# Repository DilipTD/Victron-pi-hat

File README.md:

# Victron Raspberry Pi HAT (v45.3)

A 4-layer, 85 x 56 mm Raspberry Pi 5 HAT for Victron Venus OS. It adds three VE.Direct ports, VE.Can, RS485, four low-side relay outputs, four opto-isolated inputs, a fan output, a buzzer and a plug-on 5 V / 5 A supply for the Pi, all fed from a 7-40 V battery input. Fabrication: JLCPCB. Designer: Dilip Kumar TD.

## 1. Key specification

| Item | Value |
|---|---|
| Board | 85 x 56 mm, 4 layers, 1.6 mm, KiCad 7 |
| Input | 7-40 V DC at J101, 7 A fuse F101 |
| 5 V supply | 7Semi AP64500 plug-on module U201, fixed 5.0 V, 5 A, on 5 mm pins |
| Pi | Raspberry Pi 5 (Venus OS v3.70+, raspberrypi5 image), powered only through the HAT |
| Ports | VE.Direct x3 (J301, J302, J401), RS485 (J402), VE.Can (J501), 4 relay outputs (J601), 4 opto inputs 5-30 V (J701), fan (J602) |
| Chips | 2x SC16IS752 (UARTs), MCP2515 + SN65HVD230 (CAN), SP3485 (RS485), ULN2003A (relay drivers), TLP290-4 (opto inputs), 24LC32A (HAT ID EEPROM) |
| Protection | 7 A fuse F101, 5 V TVS D201 (P6SMB6.8CA). No reverse-polarity protection and no input TVS: check polarity before connecting |

## 2. PCB design

**Stack-up (JLCPCB 4-layer, 1.6 mm):** F.Cu signals and parts, In1.Cu solid GND plane, In2.Cu +5V plane, B.Cu signals, parts and power pours. Copper: 1 oz outer, 0.5 oz inner (JLCPCB default stack-up).

**Power paths:**
- Input VIN_RAW / VIN_F / VIN_P: 1.6 mm tracks plus B.Cu pours in parallel, joined by 0.8 / 0.4 mm via arrays, sized for 4.2 A (7 V in, 5 A out).
- +5V: pours at the module output pins, then the In2.Cu +5V plane. In v45.3 the +5V also continues on F.Cu and In1.Cu at the Pi supply corner, with a copper bridge (26.5-34.5 x 58-68.5 mm) and an In1.Cu +5V pour at the U201 output (wider copper where the supply narrows).
- GND: solid In1.Cu plane, F.Cu and B.Cu pours, stitching vias on a 3 mm grid.
- 5 V branches: Pi 2.5 A, display 3 A (PTC F102), relays and fan 2 A (PTC F601).

**Signals:**
- Net classes are stored in `victron-hat.kicad_pro` (see `01-PCB-v45.0/NETCLASSES.md`): signals 0.20 mm track, 0.15 mm clearance; fieldbus pairs (CAN, RS485) 0.4 mm with 0.30 mm clearance; VE.Direct pairs 0.25 mm; pour-free corridors beside the pairs.
- Vias: 0.6 / 0.3 mm for signals, 0.8 / 0.4 mm for power, 1.0 / 0.5 mm groups for high current.
- U201 is a THT module on 5 mm pins: pins 1-3 VIN, 4-9 GND, 10-12 +5V, with 1.8 mm pads.

**Manufacturing:** JLCPCB Gerber zip, BOM and CPL are in `01-PCB-v45.0/JLCPCB/` (bottom-side economic assembly). Hand-soldered parts are listed in `HAND-SOLDER-parts.csv` (terminals, JST connectors, Pi socket, buzzer, U201 pins). Silkscreen is clipped from pads, pin-1 marks are chamfered pads, and diode cathodes are marked by a bar.

**Checks:** KiCad DRC 0 errors / 0 unconnected / 0 footprint errors on v45.3. JLCPCB's own JLCDFM and 3D assembly preview have not been run: upload the Gerber zip there before paying. Known JLCDFM items: mask-opening and "( )" warnings, and a 2.40 mm THT-to-SMD gap between U201 pin 1 and IC701 pin 9 (warning).

## 3. Voltage drop (DC copper solve, full 5 A load, v45.3)

| Net | Result |
|---|---|
| +5V output, 5.0 A total | max drop 12.6 mV at the Pi header (J201), 5.7 mV display, 5.2 mV relay; copper loss 0.047 W |
| GND return | max drop 5.1 mV; copper loss 0.022 W |
| VIN_RAW / VIN_P | a few mV (see `01-PCB-v45.0/SIMULATION`) |

Current density peaks: +5V In2 1.02 A/mm, GND In1 1.93 A/mm (above the 1.25 A/mm inner-layer guide, in a few small spots between the Pi header GND pins), GND F.Cu 2.45 A/mm (limit 2.5). The Pi header gets about 4.98 V at 5 A with U201 at 5.00 V.

## 4. Thermal

Method: 2-D thermal sheet model of the board (0.25 mm grid), component losses plus copper I2R plus the U201 module loss, with still air or a 30 mm fan. Modelled; not measured on hardware.

| Case | Result |
|---|---|
| Copper I2R only, 5 A | temperature rise at most about 1 C |
| HAT with all ICs, U201 module excluded, 40 V in, 60 C ambient | stays below 70 C |
| U201 module itself at 5 A | loses 2.4-4.7 W; about 71-111 C with fan at 25 C ambient, up to about 131-187 C in still air at 60 C ambient |

**The 5 V module is the hot spot, not the board copper.** For a continuous 5 A load, fit a heatsink on U201, add copper under it, keep the fan fitted (30 mm fan over the 28 mm cutout), or limit the continuous load to about 3 A. Reports and heat maps: `01-PCB-v45.0/SIMULATION/` (THERMAL-*.md and thermal-*.png).

## 5. Port simulation

Calculated from the routed v45.3 board: series resistors, edge times, fault currents and routed lengths for every port.

- VE.Direct (3.3 V logic, 470 R series): TX high 3.25 V; a shorted TX pin draws about 7 mA, within the SC16IS752 limit; 5 V Victron TX is accepted (5 V-tolerant input).
- RS485 (SP3485) and CAN (SN65HVD230 + MCP2515): equal-length pairs, 120 R termination by jumper (JP401 / JP501, bus end only).
- Track-length skew between signals is at most about 0.1 ns, negligible against the slowest bit time (2 us for CAN at 500 kbit/s).
- Opto inputs: apply 5-30 V DC between INx and IN COM.

## 6. Venus OS GUI

The screenshots are layout renderings with example values, not captures from real hardware. Classic GUI pages: [ALL-GUI-v1-classic-pages.png](03-GUI-screenshots/ALL-GUI-v1-classic-pages.png)

## 7. 4-relay extension board

## 8. Install (Venus OS)

1. Write the HAT ID EEPROM once from Raspberry Pi OS (bridge JP801, run `eeprom/flash-eeprom.sh`).
2. On Venus OS install kwindrem SetupHelper, then:

```
scp -r 02-VenusOS-software-v4.2 root@venus.local:/data/VictronHat
ssh root@venus.local /data/VictronHat/setup
```

3. Choose Install, reboot, then Settings > Services > VE.Can port > "VE.Can & Lynx Ion BMS".
4. Relays and inputs need kwindrem RpiGpioSetup. Test on a spare SD card first.

Port wiring: J101 7-40 V (1 = -, 2 = +); J301/J302/J401 VE.Direct JST PH 4-pin; J402 RS485 A/B/GND; J501 CANH/CANL/GND; J601 OUT1-4 (0.5 A each, low-side), +5V, GND; J701 IN COM, IN1-IN4; J602 fan 5 V. Never plug USB-C into the Pi with the HAT fitted.

## 9. Contents

| Path | Content |
|---|---|
| 01-PCB-v45.0/ | Gerbers, BOM, CPL, Schematic, checks |
| 01-PCB-v45.0/JLCPCB/ | Gerber zip to upload to JLCPCB |
| 02-VenusOS-software-v4.2/ | Venus OS package (SetupHelper) and HAT EEPROM |
| 03-GUI-screenshots/, 04-3D-preview/ | GUI renderings, 3D preview |
| 05-relay-extension-v1.2/ | relay extension board |
| 07-tool-pcb-autorouter/ | Python autorouter |

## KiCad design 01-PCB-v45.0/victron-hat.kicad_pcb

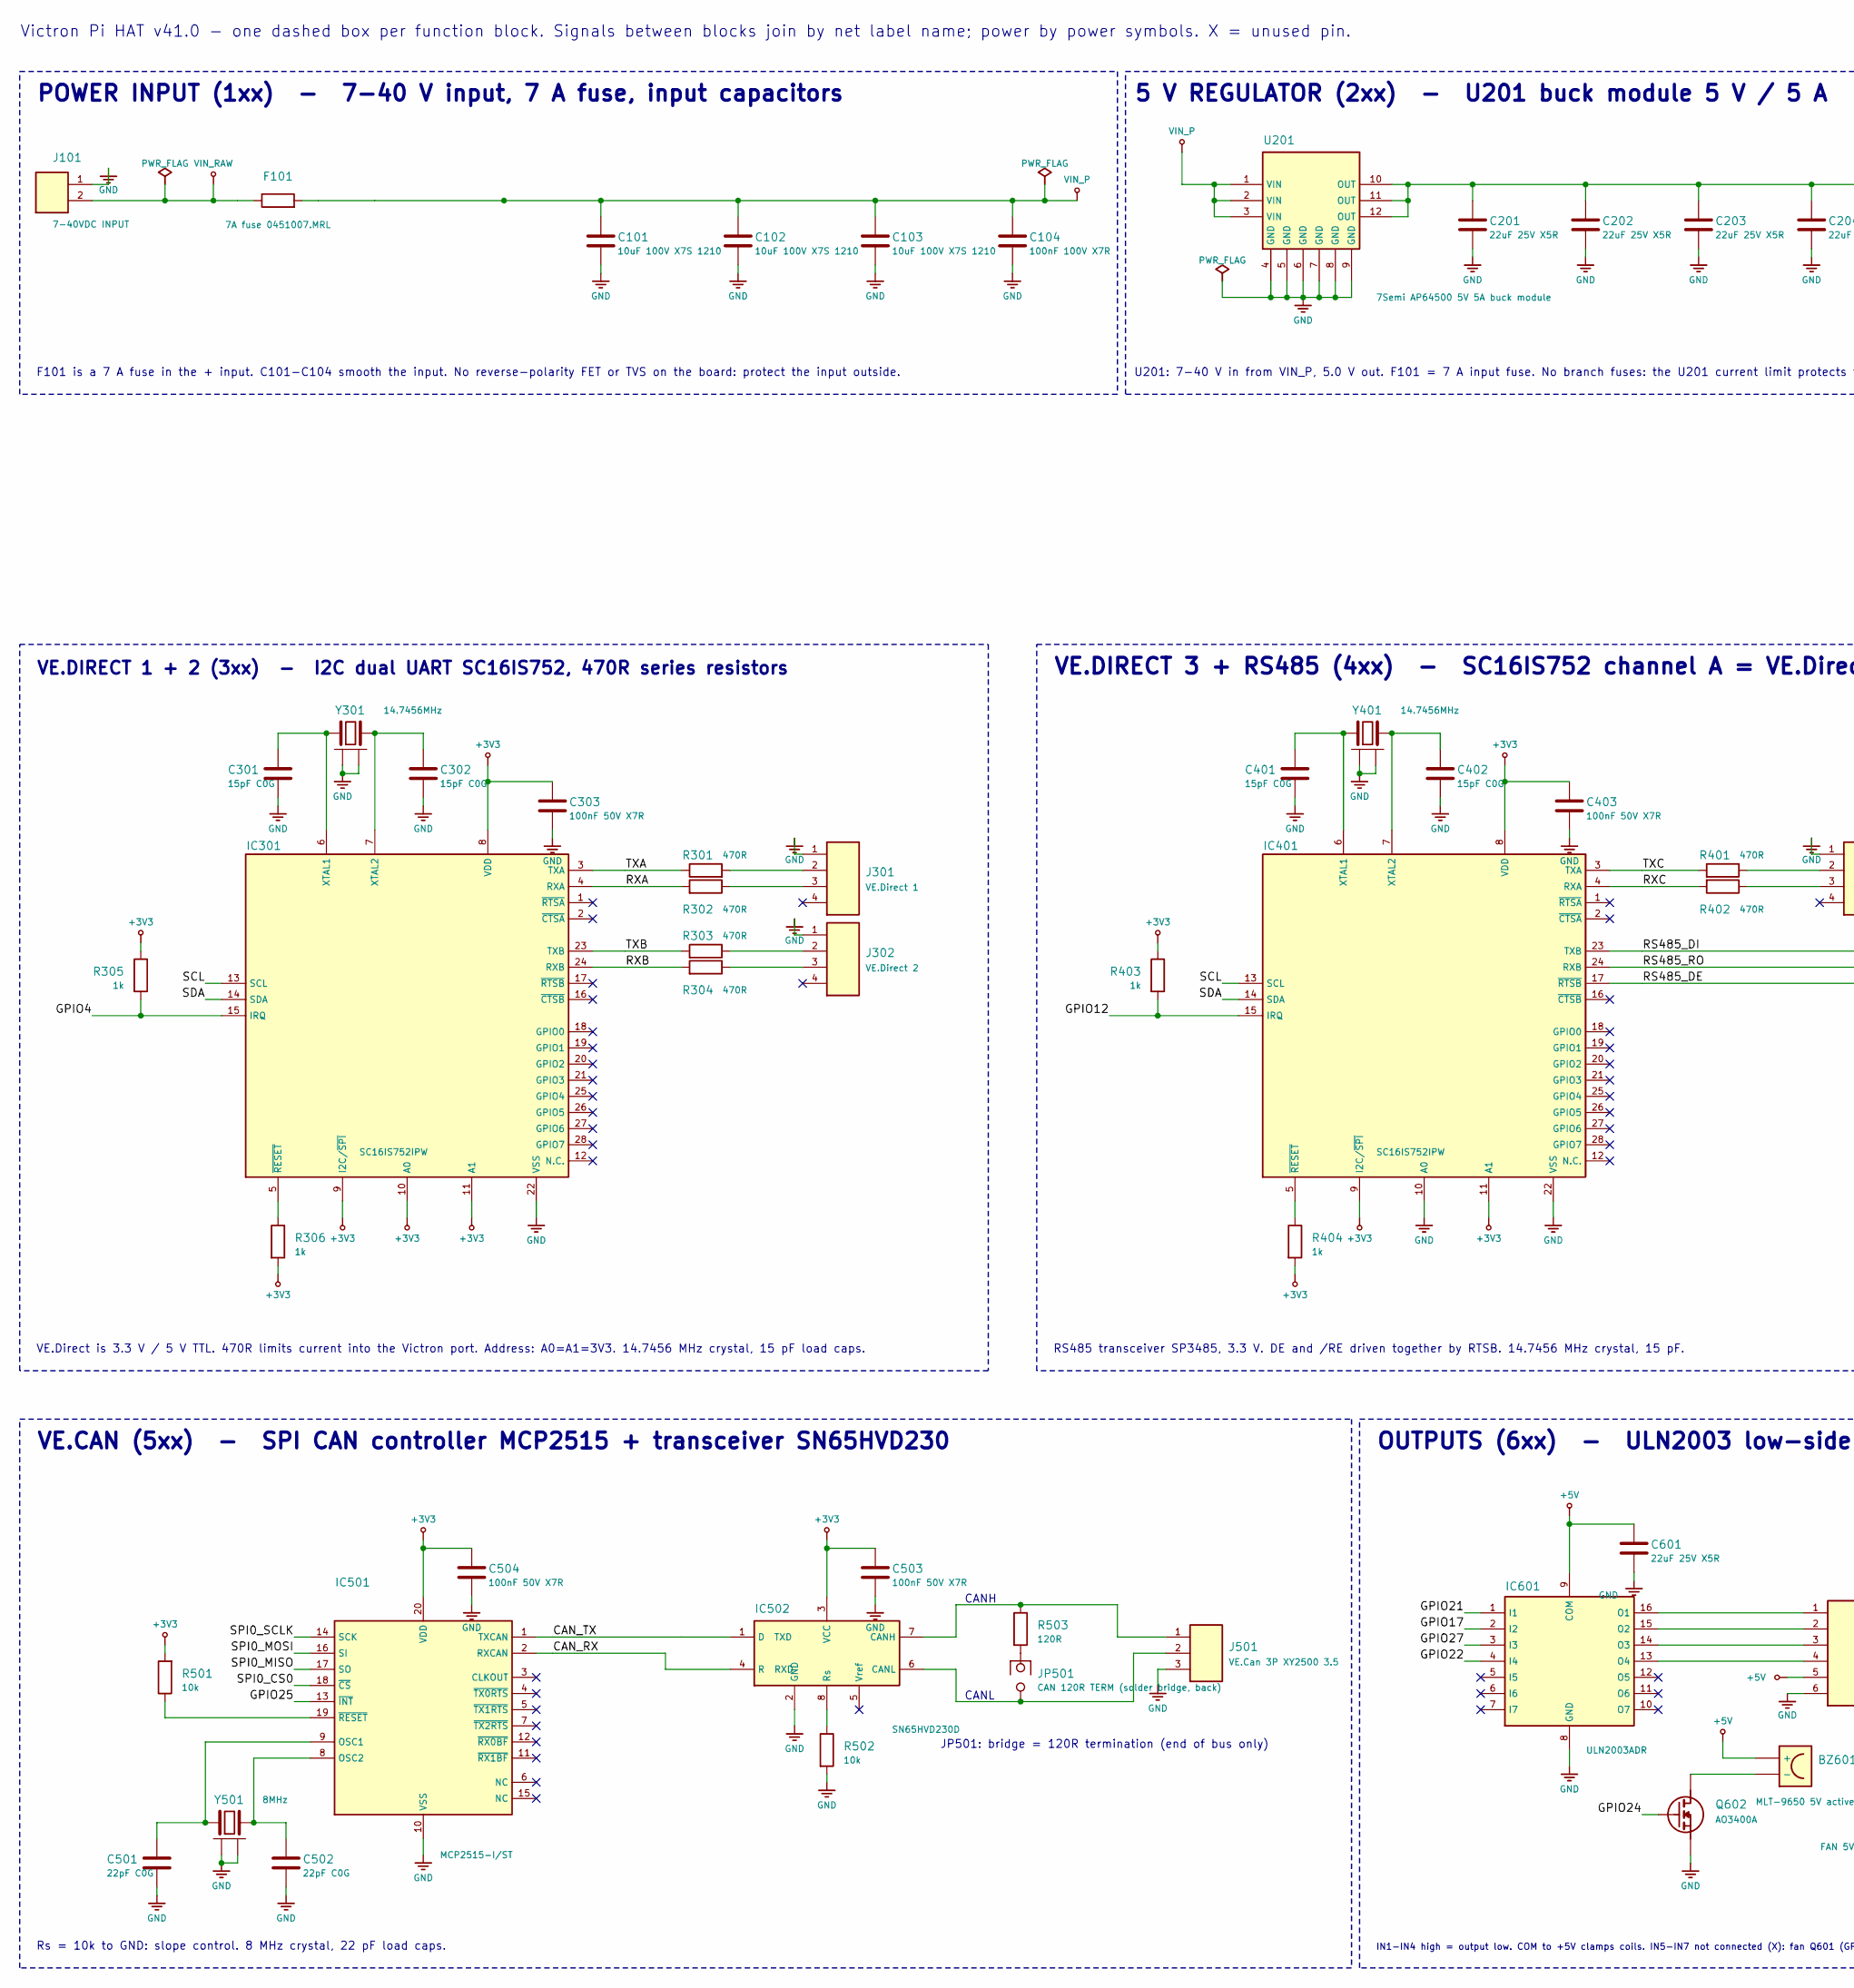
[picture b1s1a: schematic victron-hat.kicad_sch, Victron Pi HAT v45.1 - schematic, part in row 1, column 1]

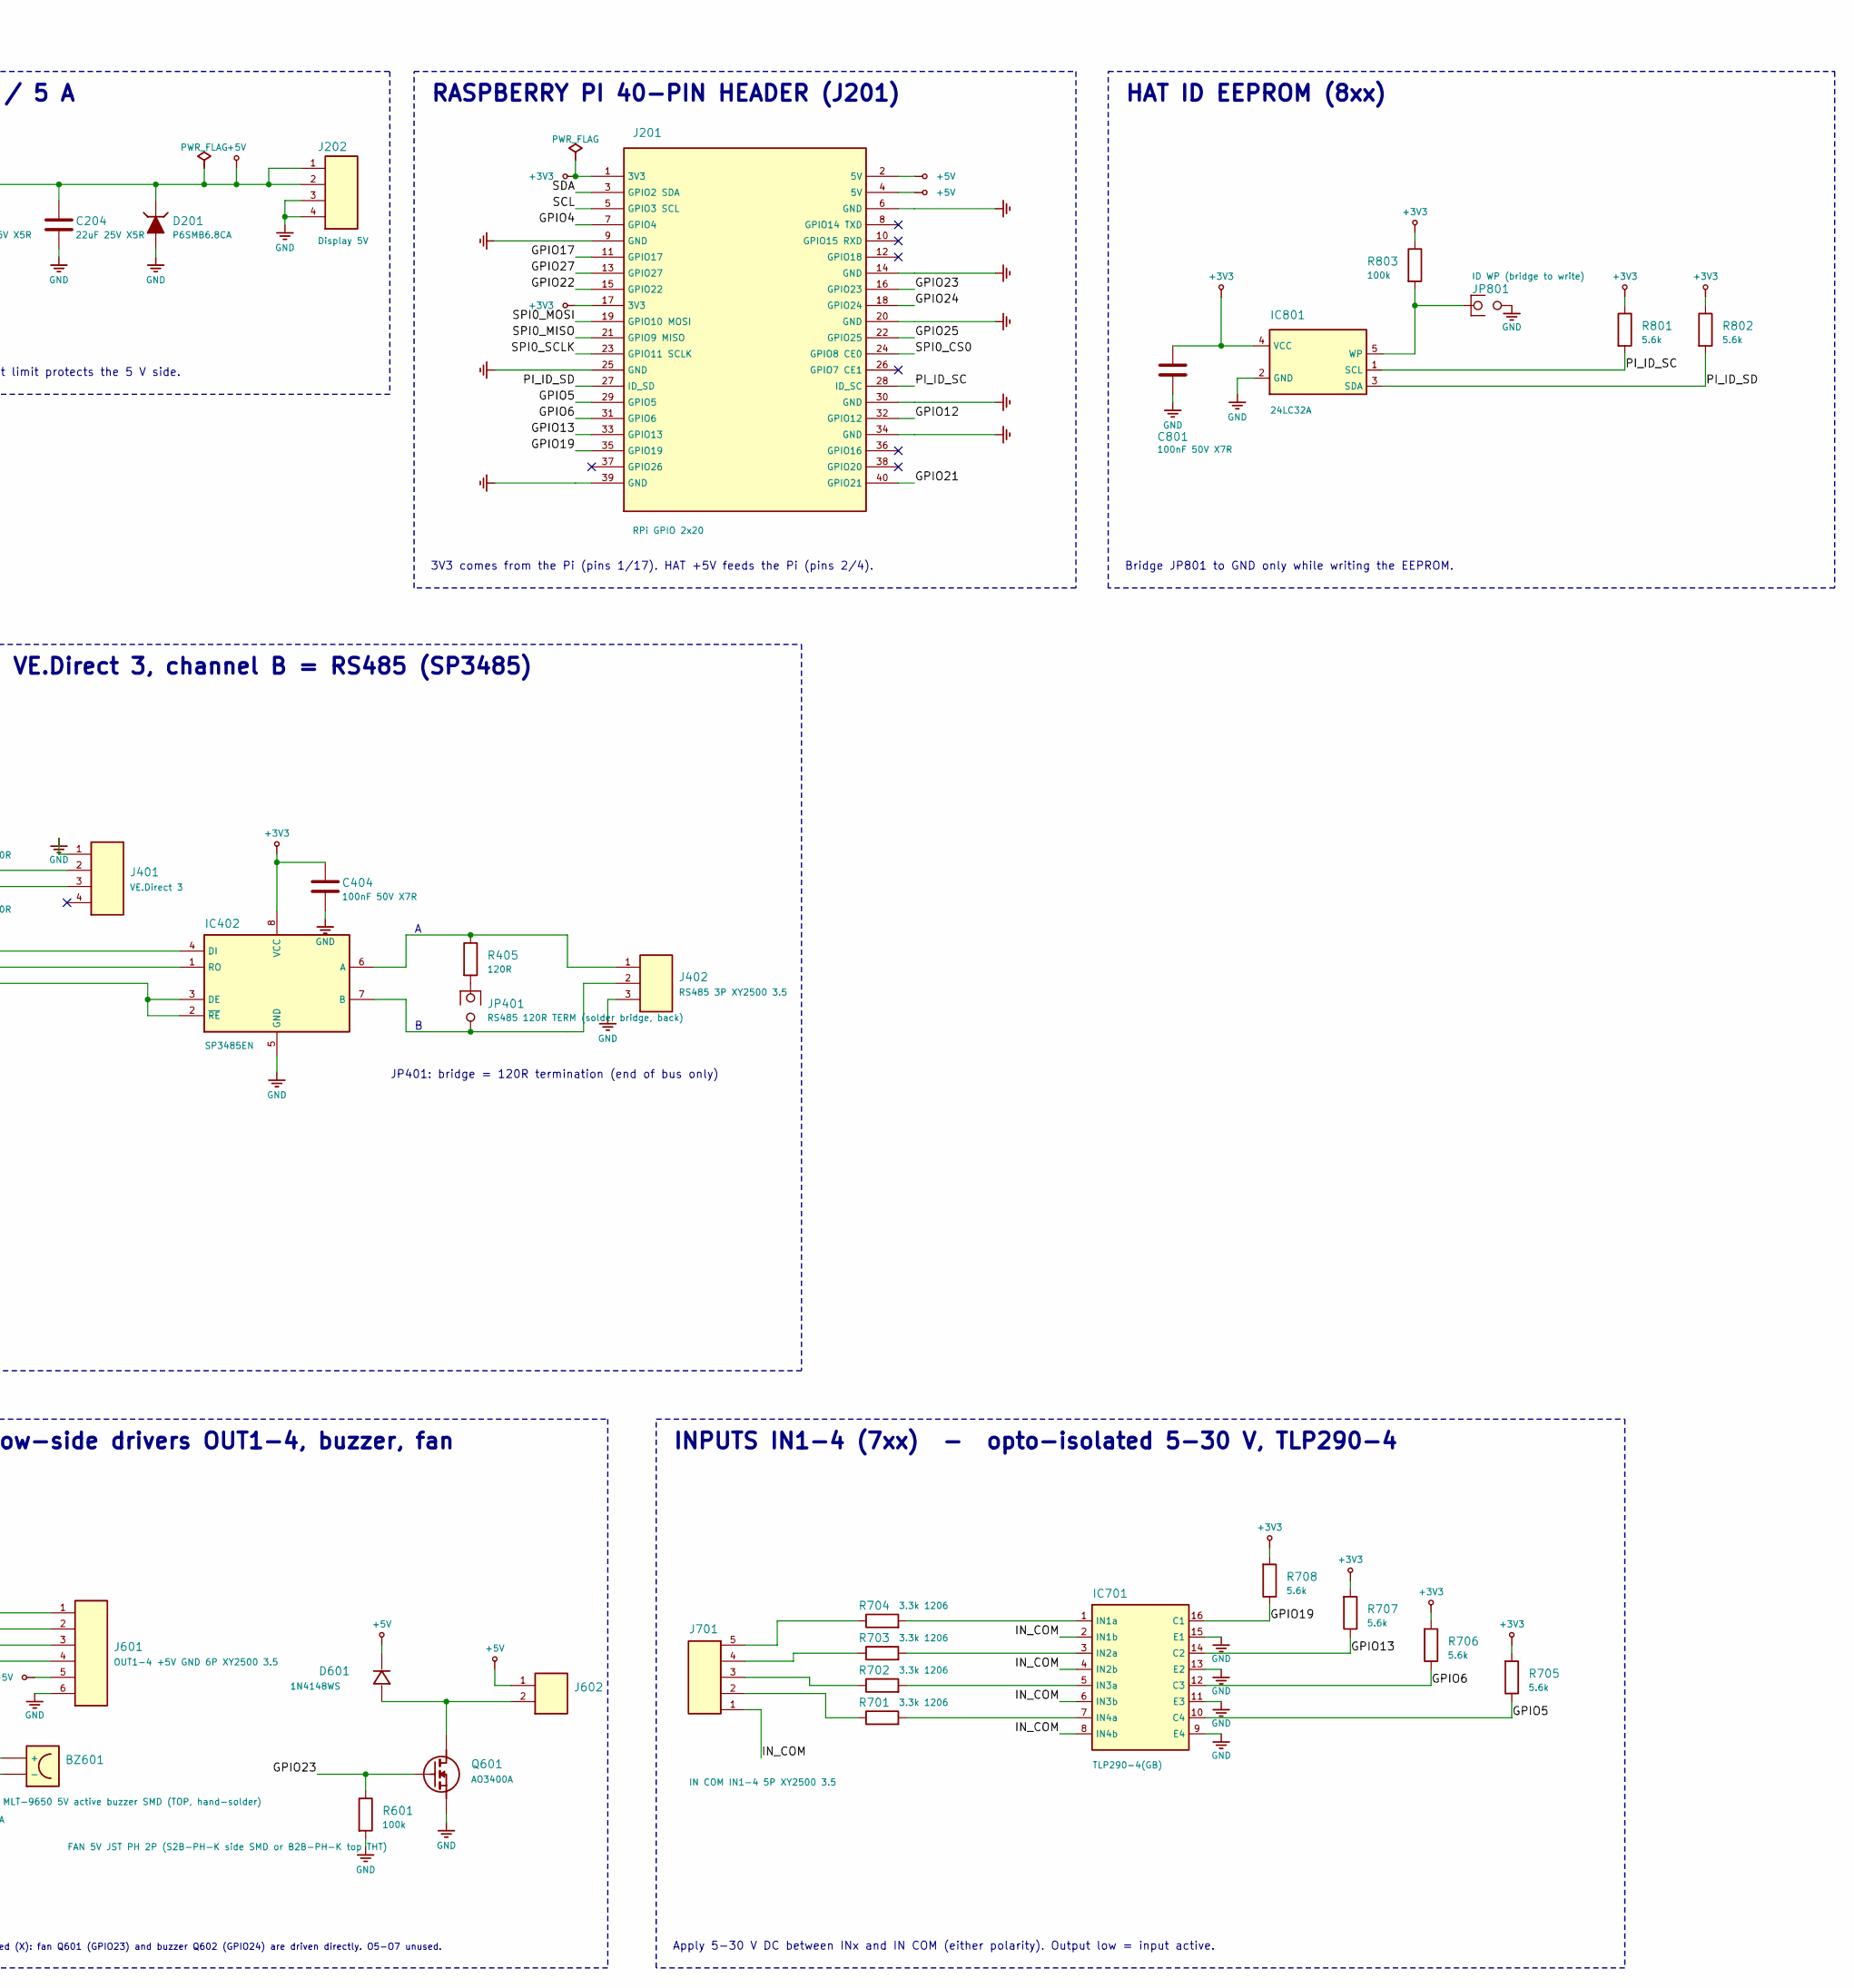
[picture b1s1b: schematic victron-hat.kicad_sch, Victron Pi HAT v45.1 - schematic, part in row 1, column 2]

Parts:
BZ601: MLT-9650 5V active buzzer SMD (TOP, hand-solder); Buzzer_SMD_9.6x9.6mm_MLT-9650; LCSC C96127
C101, C102, C103: 10uF 100V X7S 1210; C_1210_3225Metric; LCSC C576517
C104: 100nF 100V X7R; C_0805_2012Metric; LCSC C28233
C201, C202, C203, C204, C601: 22uF 25V X5R; C_0805_2012Metric; LCSC C45783
C301, C302, C401, C402: 15pF C0G; C_0805_2012Metric; LCSC C63339
C303, C403, C404, C503, C504, C801: 100nF 50V X7R; C_0805_2012Metric; LCSC C49678
C501, C502: 22pF C0G; C_0805_2012Metric; LCSC C1804
D201: P6SMB6.8CA; D_SMB; LCSC C78395
D601: 1N4148WS; D_SOD-323; LCSC C2128
F101: 7A fuse 0451007.MRL; Fuse_Littelfuse-NANO2-451_453; LCSC hand-solder
IC301, IC401: SC16IS752IPW; TSSOP-28_4.4x9.7mm_P0.65mm; LCSC C57156
IC402: SP3485EN; SOIC-8_3.9x4.9mm_P1.27mm; LCSC C8963
IC501: MCP2515-I/ST; TSSOP-20_4.4x6.5mm_P0.65mm; LCSC C185941
IC502: SN65HVD230D; SOIC-8_3.9x4.9mm_P1.27mm; LCSC C12084
IC601: ULN2003ADR; SOIC-16_3.9x9.9mm_P1.27mm; LCSC C7512
IC701: TLP290-4(GB); SOP-16_4.4x10.3mm_P1.27mm; LCSC C39031
IC801: 24LC32A; SOT-23-5; LCSC C616245
J101: 7-40VDC INPUT; PhoenixContact_MC_1,5_2-G-3.5_1x02_P3.50mm_Horizontal; LCSC C880572
J201: RPi GPIO 2x20; PinSocket_2x20_P2.54mm_Vertical
J202: Display 5V; PinHeader_1x04_P2.54mm_Vertical; LCSC C124378
J301: VE.Direct 1; JST_PH_S4B-PH-K_1x04_P2.00mm_Horizontal; LCSC C157926
J302: VE.Direct 2; JST_PH_S4B-PH-K_1x04_P2.00mm_Horizontal; LCSC C157926
J401: VE.Direct 3; JST_PH_S4B-PH-K_1x04_P2.00mm_Horizontal; LCSC C157926
J402: RS485 3P XY2500 3.5; PhoenixContact_MC_1,5_3-G-3.5_1x03_P3.50mm_Horizontal; LCSC C880573
J501: VE.Can 3P XY2500 3.5; PhoenixContact_MC_1,5_3-G-3.5_1x03_P3.50mm_Horizontal; LCSC C880573
J601: OUT1-4 +5V GND 6P XY2500 3.5; PhoenixContact_MC_1,5_6-G-3.5_1x06_P3.50mm_Horizontal
J602: FAN 5V JST PH 2P (S2B-PH-K side SMD or B2B-PH-K t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; JST_PH_S2B-PH-K_1x02_P2.00mm_Horizontal; LCSC C173752
J701: IN COM IN1-4 5P XY2500 3.5; PhoenixContact_MC_1,5_5-G-3.5_1x05_P3.50mm_Horizontal; LCSC C880575
JP401: RS485 120R TERM (solder bridge, back); SolderJumper-2_P1.3mm_Open_RoundedPad1.0x1.5mm
JP501: CAN 120R TERM (solder bridge, back); SolderJumper-2_P1.3mm_Open_RoundedPad1.0x1.5mm
JP801: ID WP (bridge to write); SolderJumper-2_P1.3mm_Open_RoundedPad1.0x1.5mm
Q601, Q602: AO3400A; SOT-23; LCSC C20917
R301, R302, R303, R304, R401, R402: 470R; R_0805_2012Metric; LCSC C17710
R305, R306, R403: 1k; R_0805_2012Metric; LCSC C17513
R404: 1k; R_0603_1608Metric; LCSC C21190
R405, R503: 120R; R_0805_2012Metric; LCSC C17437
R501, R502: 10k; R_0805_2012Metric; LCSC C17414
R601, R803: 100k; R_0603_1608Metric; LCSC C25803
R701, R702, R703, R704: 3.3k 1206; R_1206_3216Metric; LCSC C26032
R705, R706, R707, R708, R801, R802: 5.6k; R_0603_1608Metric; LCSC C23189
U201: 7Semi AP64500 5V 5A buck module; 7Semi_AP64500_Module_21x18mm
Y301, Y401: 14.7456MHz; Crystal_SMD_3225-4Pin_3.2x2.5mm; LCSC C2885591
Y501: 8MHz; Crystal_SMD_3225-4Pin_3.2x2.5mm; LCSC C2682775

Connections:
+3V3: C303.1, C403.1, C404.1, C503.1, C504.1, C801.1, IC301.8 (VDD), IC301.9 (I2C/~SPI), IC301.10 (A0), IC301.11 (A1), IC401.8 (VDD), IC401.9 (I2C/~SPI), IC401.11 (A1), IC402.8 (VCC), IC501.20 (VDD), IC502.3 (VCC), IC801.4 (VCC), J201.1 (3V3), J201.17 (3V3), R305.1, R306.2, R403.1, R404.2, R501.2, R705.1, R706.1, R707.1, R708.1, R801.1, R802.1, R803.1
+5V: BZ601.1 (+), C201.1, C202.1, C203.1, C204.1, C601.1, D201.1 (K), D601.1 (K), IC601.9 (COM), J201.2 (5V), J201.4 (5V), J202.1, J202.2, J601.5, J602.1, U201.10 (OUT), U201.11 (OUT), U201.12 (OUT)
/CAN_RX: IC501.2 (RXCAN), IC502.4 (R RXD)
/CAN_TX: IC501.1 (TXCAN), IC502.1 (D TXD)
/GPIO4: IC301.15 (IRQ), J201.7 (GPIO4), R305.2
/GPIO5: IC701.10 (C4), J201.29 (GPIO5), R705.2
/GPIO6: IC701.12 (C3), J201.31 (GPIO6), R706.2
/GPIO12: IC401.15 (IRQ), J201.32 (GPIO12), R403.2
/GPIO13: IC701.14 (C2), J201.33 (GPIO13), R707.2
/GPIO17: IC601.2 (I2), J201.11 (GPIO17)
/GPIO19: IC701.16 (C1), J201.35 (GPIO19), R708.2
/GPIO21: IC601.1 (I1), J201.40 (GPIO21)
/GPIO22: IC601.4 (I4), J201.15 (GPIO22)
/GPIO23: J201.16 (GPIO23), Q601.1 (G), R601.1
/GPIO24: J201.18 (GPIO24), Q602.1 (G)
/GPIO25: IC501.13 (~INT), J201.22 (GPIO25)
/GPIO27: IC601.3 (I3), J201.13 (GPIO27)
/IN_COM: IC701.2 (IN1b), IC701.4 (IN2b), IC701.6 (IN3b), IC701.8 (IN4b), J701.1
/PI_ID_SC: IC801.1 (SCL), J201.28 (ID_SC), R801.2
/PI_ID_SD: IC801.3 (SDA), J201.27 (ID_SD), R802.2
/RS485_DE: IC401.17 (~RTSB), IC402.2 (~RE), IC402.3 (DE)
/RS485_DI: IC401.23 (TXB), IC402.4 (DI)
/RS485_RO: IC401.24 (RXB), IC402.1 (RO)
/RXA: IC301.4 (RXA), R302.2
/RXB: IC301.24 (RXB), R304.2
/RXC: IC401.4 (RXA), R402.2
/SCL: IC301.13 (SCL), IC401.13 (SCL), J201.5 (GPIO3 SCL)
/SDA: IC301.14 (SDA), IC401.14 (SDA), J201.3 (GPIO2 SDA)
/SPI0_CS0: IC501.18 (~CS), J201.24 (GPIO8 CE0)
/SPI0_MISO: IC501.17 (SO), J201.21 (GPIO9 MISO)
/SPI0_MOSI: IC501.16 (SI), J201.19 (GPIO10 MOSI)
/SPI0_SCLK: IC501.14 (SCK), J201.23 (GPIO11 SCLK)
/TXA: IC301.3 (TXA), R301.1
/TXB: IC301.23 (TXB), R303.1
/TXC: IC401.3 (TXA), R401.1
GND: C101.2, C102.2, C103.2, C104.2, C201.2, C202.2, C203.2, C204.2, C301.2, C302.2, C303.2, C401.2, C402.2, C403.2, C404.2, C501.2, C502.2, C503.2, C504.2, C601.2, C801.2, D201.2 (A), IC301.22 (VSS), IC401.10 (A0), IC401.22 (VSS), IC402.5 (GND), IC501.10 (VSS), IC502.2 (GND), IC601.8 (GND), IC701.9 (E4), IC701.11 (E3), IC701.13 (E2), IC701.15 (E1), IC801.2 (GND), J101.1, J201.6 (GND), J201.9 (GND), J201.14 (GND), J201.20 (GND), J201.25 (GND), J201.30 (GND), J201.34 (GND), J201.39 (GND), J202.3, J202.4, J301.1, J302.1, J401.1, J402.3, J501.3, J601.6, JP801.2, Q601.2 (S), Q602.2 (S), R502.2, R601.2, U201.4 (GND), U201.5 (GND), U201.6 (GND), U201.7 (GND), U201.8 (GND), U201.9 (GND), Y301.2 (GND), Y301.4 (GND), Y401.2 (GND), Y401.4 (GND), Y501.2 (GND), Y501.4 (GND)
unnamed: BZ601.2 (-), Q602.3 (D)
unnamed: D601.2 (A), J602.2, Q601.3 (D)
unnamed: C301.1, IC301.6 (XTAL1), Y301.3
unnamed: C302.1, IC301.7 (XTAL2), Y301.1
unnamed: IC301.5 (~RESET), R306.1
unnamed: C401.1, IC401.6 (XTAL1), Y401.3
unnamed: C402.1, IC401.7 (XTAL2), Y401.1
unnamed: IC401.5 (~RESET), R404.1
unnamed: IC402.6 (A), J402.1, R405.1
unnamed: IC402.7 (B), J402.2, JP401.2
unnamed: C501.1, IC501.9 (OSC1), Y501.3
unnamed: C502.1, IC501.8 (OSC2), Y501.1
unnamed: IC501.19 (~RESET), R501.1
unnamed: IC502.7 (CANH), J501.1, R503.1
unnamed: IC502.6 (CANL), J501.2, JP501.2
unnamed: IC502.8 (Rs), R502.1
unnamed: IC601.16 (O1), J601.1
unnamed: IC601.15 (O2), J601.2
unnamed: IC601.14 (O3), J601.3
unnamed: IC601.13 (O4), J601.4
unnamed: IC701.1 (IN1a), R704.2
unnamed: IC701.3 (IN2a), R703.2
unnamed: IC701.5 (IN3a), R702.2
unnamed: IC701.7 (IN4a), R701.2
unnamed: IC801.5 (WP), JP801.1, R803.2
unnamed: J301.2, R301.2
unnamed: J301.3, R302.1
unnamed: J302.2, R303.2
unnamed: J302.3, R304.1
unnamed: J401.2, R401.2
unnamed: J401.3, R402.1
unnamed: J701.2, R701.1
unnamed: J701.3, R702.1
unnamed: J701.4, R703.1
unnamed: J701.5, R704.1
unnamed: JP401.1, R405.2
unnamed: JP501.1, R503.2
VIN_P: C101.1, C102.1, C103.1, C104.1, F101.2, U201.1 (VIN), U201.2 (VIN), U201.3 (VIN)
VIN_RAW: F101.1, J101.2

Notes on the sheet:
POWER INPUT (1xx) - 7-40 V input, 7 A fuse, input capacitors
F101 is a 7 A fuse in the + input. C101-C104 smooth the input. No reverse-polarity FET or TVS on the board: protect the input outside.
5 V REGULATOR (2xx) - U201 buck module 5 V / 5 A
U201: 7-40 V in from VIN_P, 5.0 V out. F101 = 7 A input fuse. No branch fuses: the U201 current limit protects the 5 V side.
RASPBERRY PI 40-PIN HEADER (J201)
3V3 comes from the Pi (pins 1/17). HAT +5V feeds the Pi (pins 2/4).
HAT ID EEPROM (8xx)
Bridge JP801 to GND only while writing the EEPROM.
VE.DIRECT 1 + 2 (3xx) - I2C dual UART SC16IS752, 470R series resistors
VE.Direct is 3.3 V / 5 V TTL. 470R limits current into the Victron port. Address: A0=A1=3V3. 14.7456 MHz crystal, 15 pF load caps.
VE.DIRECT 3 + RS485 (4xx) - SC16IS752 channel A = VE.Direct 3, channel B = RS485 (SP3485)
JP401: bridge = 120R termination (end of bus only)
RS485 transceiver SP3485, 3.3 V. DE and /RE driven together by RTSB. 14.7456 MHz crystal, 15 pF.
VE.CAN (5xx) - SPI CAN controller MCP2515 + transceiver SN65HVD230
CANH
CANL
JP501: bridge = 120R termination (end of bus only)
Rs = 10k to GND: slope control. 8 MHz crystal, 22 pF load caps.
OUTPUTS (6xx) - ULN2003 low-side drivers OUT1-4, buzzer, fan
IN1-IN4 high = output low. COM to +5V clamps coils. IN5-IN7 not connected (X): fan Q601 (GPIO23) and buzzer Q602 (GPIO24) are driven directly. O5-O7 unused.
INPUTS IN1-4 (7xx) - opto-isolated 5-30 V, TLP290-4
Apply 5-30 V DC between INx and IN COM (either polarity). Output low = input active.
Victron Pi HAT v41.0 - one dashed box per function block. Signals between blocks join by net label name; power by power symbols. X = unused pin.

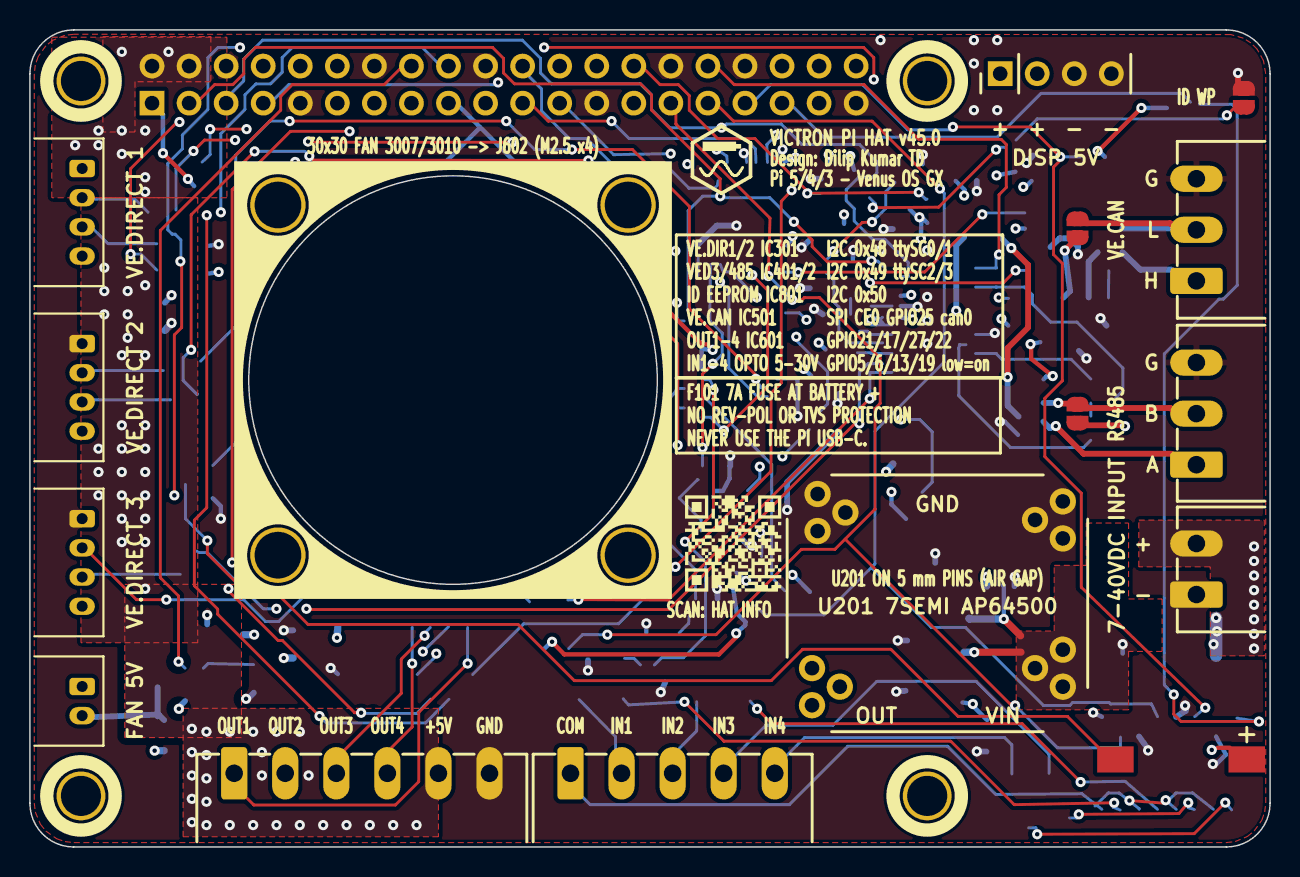
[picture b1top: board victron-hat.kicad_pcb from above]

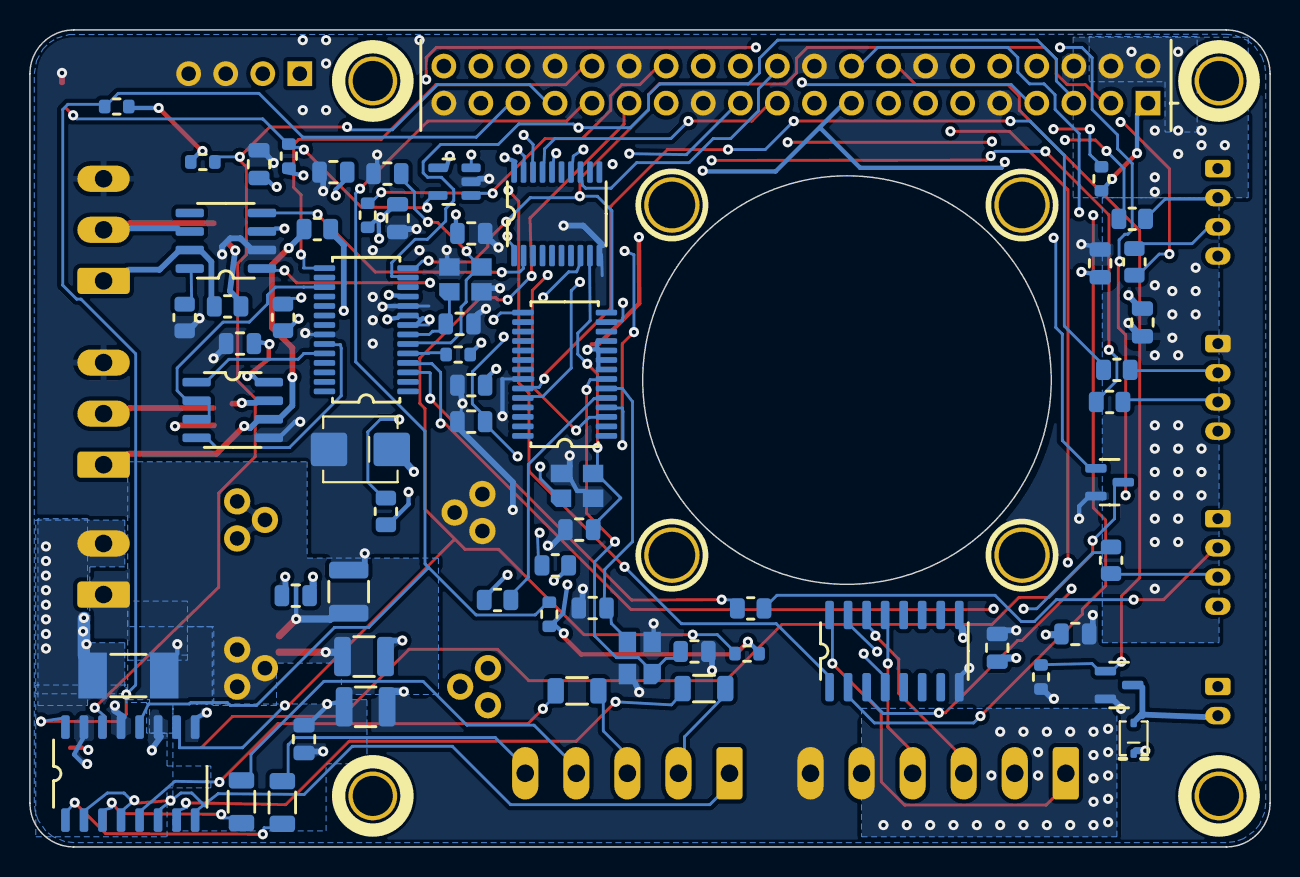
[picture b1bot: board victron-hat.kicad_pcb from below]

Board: 4 copper layers, 85.0 x 56.0 mm, 88 parts (64 on the bottom side), 75 nets.

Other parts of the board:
FAN1: 30x30x10 fan (3D only); Fan_30x30_3D_only
MH1, MH2, MH3, MH4: MountingHole_2.75mm_M2.5
MH5, MH6, MH7, MH8: Fan hole 3.2mm (M2.5/M3); MountingHole_3.2mm_Fan

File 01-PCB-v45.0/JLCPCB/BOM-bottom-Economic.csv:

Comment,Designator,Footprint,LCSC Part #
GRM32EC72A106KE05L 10uF 100V X7S 1210,"C101,C102,C103",C_1210_3225Metric,C576517
CL21B104KCFNNNE 100nF 100V X7R 0805 (Basic),C104,C_0805_2012Metric,C28233
CL21A226MAQNNNE 22uF 25V X5R 0805 (Basic),"C201,C202,C203,C204,C601",C_0805_2012Metric,C45783
0805CG150J500NT 15pF 50V C0G,"C301,C302,C401,C402",C_0805_2012Metric,C63339
CC0805KRX7R9BB104 100nF 50V X7R (as v19.1),"C303,C403,C404,C503,C504,C801",C_0805_2012Metric,C49678
CL21C220JBANNNC 22pF 50V C0G,"C501,C502",C_0805_2012Metric,C1804
"P6SMB6.8CA TVS 6.8V bidirectional SMB (+5V, as v19.1)",D201,D_SMB,C78395
1N4148WS 75V 150mA SOD-323 (fan flyback),D601,D_SOD-323,C2128
"SC16IS752IPW,128","IC301,IC401",TSSOP-28_4.4x9.7mm_P0.65mm,C57156
SP3485EN-L/TR,IC402,SOIC-8_3.9x4.9mm_P1.27mm,C8963
MCP2515T-I/ST,IC501,TSSOP-20_4.4x6.5mm_P0.65mm,C185941
SN65HVD230DR,IC502,SOIC-8_3.9x4.9mm_P1.27mm,C12084
ULN2003ADR 7x Darlington SOIC-16 (as v19.1),IC601,SOIC-16_3.9x9.9mm_P1.27mm,C7512
"TLP290-4(GB-TP,E) 4-ch AC-input optocoupler SOP-16",IC701,SOP-16_4.4x10.3mm_P1.27mm,C39031
24LC32AT-I/OT 32kbit I2C EEPROM SOT-23-5,IC801,SOT-23-5,C616245
AO3400A 30V N-MOSFET logic-level SOT-23 (fan switch + buzzer switch),"Q601,Q602",SOT-23,C20917
0805W8F4700T5E 470R 1%,"R301,R302,R303,R304,R401,R402",R_0805_2012Metric,C17710
0805W8F1001T5E 1k 1%,"R305,R306,R403",R_0805_2012Metric,C17513
0805W8F1200T5E 120R 1%,"R405,R503",R_0805_2012Metric,C17437
0805W8F1002T5E 10k 1% (as v19.1),"R501,R502",R_0805_2012Metric,C17414
0603WAF1003T5E 100k 1% 0603 (fan gate pulldown + EEPROM WP),"R601,R803",R_0603_1608Metric,C25803
1206W4F3301T5E 3.3k 1% 1206 0.25W (input series),"R701,R702,R703,R704",R_1206_3216Metric,C26032
"0603WAF5601T5E 5.6k 1% 0603 (opto pull-ups, ID I2C pull-ups, as v19.1)","R705,R706,R707,R708,R801,R802",R_0603_1608Metric,C23189
0603WAF1001T5E 1k 1% 0603,R404,R_0603_1608Metric,C21190
X3225147456MOB4SI 14.7456MHz 12pF 3225,"Y301,Y401",Crystal_SMD_3225-4Pin_3.2x2.5mm,C2885591
X32258MOB4SI 8MHz 12pF 3225,Y501,Crystal_SMD_3225-4Pin_3.2x2.5mm,C2682775

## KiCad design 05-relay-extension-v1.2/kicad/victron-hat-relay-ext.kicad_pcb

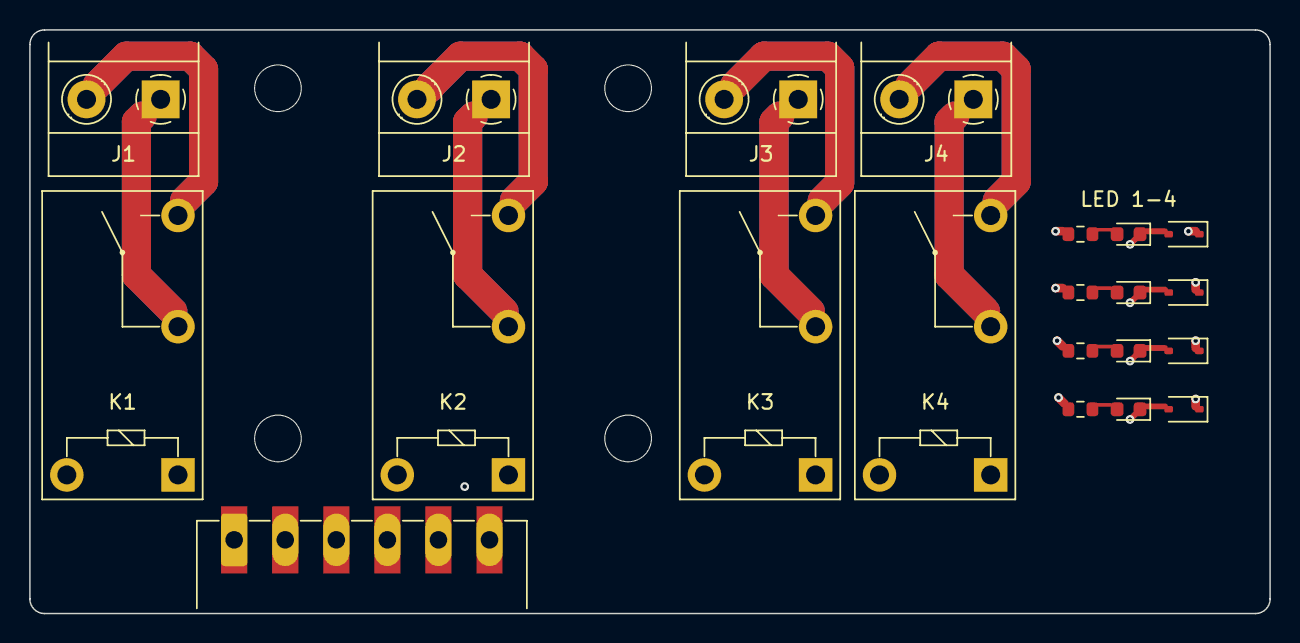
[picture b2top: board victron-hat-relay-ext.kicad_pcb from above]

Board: 4 copper layers, 85.0 x 40.0 mm, 25 parts (0 on the bottom side), 17 nets.

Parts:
D1, D2, D3, D4: 1N4148WS; D_SOD-323
H1, H2, H3, H4: M2.5 3.2 mm; MountingHole_3.2mm_Fan
J1, J2, J3, J4: MKDS 1,5/2-5.08; TerminalBlock_Phoenix_MKDS-1,5-2-5.08_1x02_P5.08mm_Horizont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
J5: MC 1,5/6-G-3.5 (cable to HAT J601); PhoenixContact_MC_1,5_6-G-3.5_1x06_P3.50mm_Horizontal
K1, K2, K3, K4: G5Q-1A4-EU DC5; Relay_SPST_Omron-G5Q-1A
LED1, LED2, LED3, LED4: green; LED_0603_1608Metric
R1, R2, R3, R4: 1k; R_0603_1608Metric

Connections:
+5V: D1.1, D2.1, D3.1, D4.1, J5.5, K1.5, K2.5, K3.5, K4.5, R1.1, R2.1, R3.1, R4.1
/CH1_COM: J1.1, K1.2
/CH1_NO: J1.2, K1.3
/CH2_COM: J2.1, K2.2
/CH2_NO: J2.2, K2.3
/CH3_COM: J3.1, K3.2
/CH3_NO: J3.2, K3.3
/CH4_COM: J4.1, K4.2
/CH4_NO: J4.2, K4.3
/OUT1: D1.2, J5.1, K1.1, LED1.1
/OUT2: D2.2, J5.2, K2.1, LED2.1
/OUT3: D3.2, J5.3, K3.1, LED3.1
/OUT4: D4.2, J5.4, K4.1, LED4.1
unnamed: LED1.2, R1.2
unnamed: LED2.2, R2.2
unnamed: LED3.2, R3.2
unnamed: LED4.2, R4.2

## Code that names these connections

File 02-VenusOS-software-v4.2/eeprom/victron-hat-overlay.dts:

/*
 * Victron Pi HAT v24.1 - device-tree overlay stored in the HAT ID EEPROM (IC801).
 * The Pi firmware applies it at boot, so /u-boot/config.txt needs no dtoverlay lines.
 *   I2C1 (GPIO2/3): SC16IS752 @0x48 (IRQ GPIO4)  -> ttySC0/ttySC1 (J301, J302)
 *                   SC16IS752 @0x49 (IRQ GPIO12) -> ttySC2/ttySC3 (J401, J402 RS485)
 *   SPI0 CE0:       MCP2515 (IRQ GPIO25)         -> can0 (J501 VE.Can)
 *   SPI0 CE1:       unused on board v28.0 (was the MCP3208 ADC1); spidev0.1 stays free
 *   SPI0 CE2:       unused on board v28.0 (was ADC2, CS = GPIO16); spidev0.2 stays free
 *   v29.4 crystals: both SC16IS752 = 14.7456 MHz (Y301, Y401), MCP2515 = 8 MHz (Y501).
 */
/dts-v1/;
/plugin/;

/ {
	compatible = "brcm,bcm2835";

	fragment@0 {
		target-path = "/";
		__overlay__ {
			victron_hat_xtal: victron_hat_xtal {
				compatible = "fixed-clock";
				#clock-cells = <0>;
				clock-frequency = <14745600>;	/* SC16IS752 Y301/Y401 */
			};
			victron_hat_can_xtal: victron_hat_can_xtal {
				compatible = "fixed-clock";
				#clock-cells = <0>;
				clock-frequency = <8000000>;	/* MCP2515 Y501 */
			};
		};
	};

	fragment@1 {
		target = <&gpio>;
		__overlay__ {
			victron_hat_uart_irq: victron_hat_uart_irq {
				brcm,pins = <4 12>;
				brcm,function = <0>;	/* input */
				brcm,pull = <2>;	/* pull-up */
			};
			victron_hat_can_irq: victron_hat_can_irq {
				brcm,pins = <25>;
				brcm,function = <0>;	/* input */
				brcm,pull = <0>;
			};
		};
	};

	fragment@2 {
		target = <&i2c_arm>;
		__overlay__ {
			#address-cells = <1>;
			#size-cells = <0>;
			status = "okay";

			sc16is752@48 {
				compatible = "nxp,sc16is752";
				reg = <0x48>;
				clocks = <&victron_hat_xtal>;
				interrupt-parent = <&gpio>;
				interrupts = <4 2>;	/* falling edge */
				pinctrl-names = "default";
				pinctrl-0 = <&victron_hat_uart_irq>;
				gpio-controller;
				#gpio-cells = <2>;
			};

			sc16is752@49 {
				compatible = "nxp,sc16is752";
				reg = <0x49>;
				clocks = <&victron_hat_xtal>;
				interrupt-parent = <&gpio>;
				interrupts = <12 2>;	/* falling edge */
				/* channel B = J402 RS485: RTSB drives SP3485 DE + /RE (active high).
				 * Auto RS-485 direction with RTS HIGH while sending = kernel
				 * "rts-active-low" (sets EFCR RTSINVER). Also applies to channel A
				 * (VE.Direct 3), whose RTSA pin is unused; rx-during-tx keeps it full duplex. */
				linux,rs485-enabled-at-boot-time;
				rs485-rts-active-low;
				rs485-rx-during-tx;
				gpio-controller;
				#gpio-cells = <2>;
			};
		};
	};

	fragment@3 {
		target = <&spidev0>;
		__overlay__ {
			status = "disabled";
		};
	};

	fragment@4 {
		target = <&spi0>;
		__overlay__ {
			#address-cells = <1>;
			#size-cells = <0>;
			status = "okay";
			cs-gpios = <&gpio 8 1>, <&gpio 7 1>, <&gpio 16 1>;	/* CE0, CE1, CE2 = GPIO16 (v27.2 MCP3204) */

			spidev@2 {
				compatible = "rohm,dh2228fv";	/* plain spidev -> /dev/spidev0.2 */
				reg = <2>;
				spi-max-frequency = <1000000>;
			};

			mcp2515@0 {
				compatible = "microchip,mcp2515";
				reg = <0>;
				pinctrl-names = "default";
				pinctrl-0 = <&victron_hat_can_irq>;
				spi-max-frequency = <10000000>;
				interrupt-parent = <&gpio>;
				interrupts = <25 8>;	/* level low */
				clocks = <&victron_hat_can_xtal>;
			};
		};
	};
	fragment@5 {
		target = <&spidev1>;
		__overlay__ {
			status = "okay";
			spi-max-frequency = <1000000>;
		};
	};
};
